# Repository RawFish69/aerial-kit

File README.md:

#  Aerial Kit

**UAS Controller, Planner, Simulator, Firmware & Configurator** - an open-source stack for aerial robots, from planning a path in simulation to configuring the flight controller.

## Demo

### Python simulation

Autonomous flight - plan a path, then fly it:

<table>
  <tr>
    <td width="50%" align="center"></td>
    <td width="50%" align="center"></td>
  </tr>
  <tr>
    <td valign="top"><em>RRT* through forest terrain on the RotorPy backend.</em></td>
    <td valign="top"><em>RRT* over mountains - the planner climbs a 47 m ridge to reach the goal. Planned path dashed in orange, flown trajectory in cyan.</em></td>
  </tr>
</table>

Standalone Python sim (Matplotlib 3D, follow camera):

<table>
  <tr>
    <td width="50%" align="center"></td>
    <td width="50%" align="center"></td>
  </tr>
  <tr>
    <td valign="top"><em>Native multirotor backend - a 56 m climbing turn, teal trail showing where it has flown. Each propeller is coloured by thrust (grey idle → yellow → orange → red).</em></td>
    <td valign="top"><em><a href="examples/fixed_wing">Twin-wing example</a> on the same renderer - banked 50° through the turn, flown path behind it, motors on the same colour map.</em></td>
  </tr>
</table>

### Custom 2.4 GHz LoRa / ELRS radio hardware

The Aerial Kit 2.4 GHz USB transceiver is a fabricated
**ESP32-S3-MINI-1U + SX1280 + RFX2401C** four-layer board. Its paired firmware
includes an RF-off hardware diagnostic plus separate ExpressLRS TX and RX
images, all built from a pinned upstream revision.

Fabricated Rev A3 boards: ESP32-S3 module and USB-C side, alongside the
SX1280/RFX2401C RF and control side.

<table>
  <tr>
    <td width="50%" align="center"></td>
    <td width="50%" align="center"></td>
  </tr>
  <tr>
    <td valign="top"><em>Rev A3 front: USB-C, ESP32-S3 module, role select, boot control and breakout pads.</em></td>
    <td valign="top"><em>Rev A3 back: SX1280 transceiver, RFX2401C front end, RF matching network and U.FL output.</em></td>
  </tr>
</table>

[Hardware sources and pinout](hardware/overlays/elrs-usb-tx/rev-a3/) ·
[Diagnostic, ExpressLRS TX and RX firmware](firmware/elrs-usb-tx-rev-a3/)

### Web configurator

[**Open the configurator**](https://rawfish69.github.io/aerial-kit/) · [Guide](docs/web-configurator.md)

Live attitude, receiver, sensors and parameter editing in the browser, over USB. Screenshots use the built-in demo board.

<table>
  <tr>
    <td width="50%"></td>
    <td width="50%"></td>
  </tr>
  <tr>
    <td><em>Classic theme.</em></td>
    <td><em>OG theme. A dark Modern theme is the default.</em></td>
  </tr>
</table>

### Hovering & Landing (IMU + Barometer + GPS)

https://github.com/user-attachments/assets/44837663-b281-45db-9803-5aaa9812833d

*Autonomous hover and landing, commanded over the CRSF/ESP-NOW link. The state estimate fuses IMU
attitude, barometric altitude, and GPS position.*

### ROS navigation

## What's in this repo

- **Controller** - standalone Python and ROS 2 control: PID, LQR, MPC, constrained MPC and MPPI, plus L1/TECS for fixed wing. The [`uav_control`](ros2_ws/src/uav_control/README.md) ROS 2 package flies missions with the constrained MPC or MPPI.
- **Planner** - straight, A*, RRT, RRT* and Dubins paths with shared terrain models.
- **Simulator** - Python simulation without ROS, plus ROS 2 fast, Gazebo and MuJoCo backends: FPV, micro long-range, research hex/octo multirotors and twin/single-motor flying wings, flyable autonomously or by keyboard.
- **AK Firmware** - our custom C flight controller, for Feather F405 and ESP32DEV, with a portable control core and image checks.
- **ELRS USB TX Rev A3** - custom ESP32-S3 + SX1280 + RFX2401C transceiver
  hardware and pinned ExpressLRS firmware target.
- **Web configurator** - live attitude, diagnostics and parameter editing over USB or a local bridge; includes a demo board.

The ROS-free control package is also on [PyPI](https://pypi.org/project/aerial-kit/): `pip install aerial-kit` or `pip install "aerial-kit[sim]"`.

## Autopilot & firmware support

| Platform | Integration | Guide |
| --- | --- | --- |
| **AK Firmware** | Custom flight-controller firmware + web configurator | [Guide](docs/flight-controller-firmware.md) |
| Betaflight | CRSF over ESP-NOW / UDP relay | [Guide](docs/HARDWARE.md) |
| PX4 | MAVLink over USB / UART / telemetry radio | [Guide](ros2_ws/src/mavlink_bridge/README.md) |
| ArduPilot | MAVLink through the same backend | [Guide](ros2_ws/src/mavlink_bridge/README.md) |
| ESP32 radio links | ESP-NOW, ELRS, LoRa and GPS | [Guide](firmware/legacy/README.md) |
| **Aerial Kit ELRS USB TX Rev A3** | Custom hardware, RF-off diagnostic, ELRS TX/RX images and native-USB bench tools | [Firmware](firmware/elrs-usb-tx-rev-a3/README.md) · [Bench](docs/RADIO-BENCH.md) |
| **Python protocol clients** | CRSF, Aerial Kit, MAVLink and gated-write MSP | [Protocol guide](docs/PROTOCOLS.md) |

## Start here

| Explore | Guide |
| --- | --- |
| Run a simulator or controller | [Software guide](docs/SOFTWARE_GUIDE.md) · [Examples](docs/EXAMPLE_USAGE.md) |
| Build AK firmware | [Firmware quick start & board status](docs/flight-controller-firmware.md) |
| Configure a board | [Web configurator quick start](docs/web-configurator.md) · [Build & deployment](apps/configurator/docs/BUILD-AND-DEPLOY.md) |
| Connect Python to firmware | [USB telemetry and attitude example](examples/firmware/) |
| Hardware designs and overlays | [Hardware workspace](hardware/) |
| Understand the stack | [Architecture, airframes, ROS 2 and roadmap](docs/STACK-GUIDE.md) |
| Connect hardware | [Hardware guide](docs/HARDWARE.md) · [Radio firmware](firmware/legacy/README.md) |
| Query radios and vehicles from Python | [Protocol examples](examples/comms/) · [Protocol guide](docs/PROTOCOLS.md) |
| Use the logo | [Branding & SVG assets](docs/branding.md) |

## Python protocol client

`aerial_kit.comms` provides one Python boundary for ELRS/CRSF radios, Aerial
Kit and Betaflight flight controllers, PX4/ArduPilot over MAVLink, and MSP
devices. Reads are safe by default; every mutation has an explicit gate.
The console can query a radio or flight controller directly:

```bash
pip install "aerial-kit[radio,mavlink]"
ak radio status --port /dev/ttyACM0
ak radio uid --port /dev/ttyACM0 --role tx
ak radio uid --port /dev/ttyACM1 --role rx
ak radio diag --port /dev/ttyACM0 --role tx
ak radio monitor --port /dev/ttyACM0 --duration 5 --json monitor.json
ak radio drive --port /dev/ttyACM0 --hz 150 --duration 10 --write
ak radio drive --port /dev/ttyACM0 --profile betaflight --write
ak radio teleop --port /dev/ttyACM0 --profile betaflight --duration 30 --write --confirm-arm
ak doctor                                   # list serial endpoints, no port opening
ak doctor --probe /dev/ttyACM0              # read-only radio/AKP/Betaflight probe
ak fc status --port /dev/ttyACM0             # auto-detects AKP or MSP
ak fc status --port /dev/ttyACM0 --protocol betaflight
ak fc params --port /dev/ttyACM0             # Aerial Kit indexed table
ak fc params --port /dev/ttyACM0 --name failsafe_throttle
ak fc get failsafe_throttle --port /dev/ttyACM0
ak fc set failsafe_throttle 1200 --port /dev/ttyACM0 --write
ak fc save --port /dev/ttyACM0 --write
ak fc preflight --port /dev/ttyACM0 --protocol betaflight --json fc-preflight.json
ak fc rc --port /dev/ttyACM0 --protocol betaflight --json fc-rc.json
ak sim --no-show
```

Use `--radio /dev/ttyUSB0` with `fc` to carry Aerial Kit requests over an ELRS
link. `fc` auto-detects Aerial Kit AKP and Betaflight MSP; `--protocol akp` or
`--protocol betaflight` removes the probe wait. MSP has no command that lists
all setting names, so Betaflight settings are read by name. Mutations require
`--write`; omitting it refuses before a frame is sent, and the CLI also refuses
configuration writes while the board reports itself armed. A successful
Betaflight setting reply is the read-back, while save remains a separate
`MSP_EEPROM_WRITE` operation. Bind and UID writes reconnect after the module
reboot and fail unless the six-byte UID reads back exactly. `aerial-kit-link`,
`aerial-kit-sim` and `aerial-kit-teleop` remain compatibility commands; new
scripts should use `ak`.

Betaflight MSP status does not contain a receiver-link-live field. `ak fc
status` therefore prints `link=unknown` for Betaflight instead of inferring a
healthy link from a successful USB response. Use `ak fc rc` for a fresh channel
observation and `ak fc preflight` to decode Betaflight arming-disable flags;
failsafe and receiver-failsafe bits make preflight exit nonzero.

`ak radio teleop` is the live keyboard path through a CRSF transmitter. It
starts disarmed; press Enter to arm after the low-throttle hold. A/D, W/S and
Q/E step roll, pitch and yaw, R/F change throttle, C neutralises the sticks,
and X immediately disarms and exits. Timeout, Ctrl-C, panic and transport
errors all attempt a final disarmed frame. The command is bounded by
`--duration` and requires both `--write` and `--confirm-arm`. The existing
`ak teleop` command remains simulator-only.

`ak doctor` lists `/dev/serial/by-id` aliases, raw ACM/USB paths, read/write
permissions and optional protocol dependencies without opening a port. Add
`--probe PATH` only when a read-only identification attempt is intended; it
tries CRSF device information, Aerial Kit AKP and Betaflight MSP in that order.

See [docs/PROTOCOLS.md](docs/PROTOCOLS.md) for framing,
transport and safety details. Native-USB radio monitor, drive, capture,
telemetry injection and two-board evidence are covered in
[docs/RADIO-BENCH.md](docs/RADIO-BENCH.md).

## Licence

The Python/ROS stack and existing link projects retain the root [MIT licence](LICENSE). AK flight-controller firmware and the web configurator are **GPL-3.0-or-later**, each with its own [firmware](firmware/LICENSE) and [configurator](apps/configurator/LICENSE) licence. Third-party notices stay with their components.

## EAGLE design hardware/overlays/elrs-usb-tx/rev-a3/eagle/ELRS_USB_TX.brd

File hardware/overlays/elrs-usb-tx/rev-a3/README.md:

# ELRS USB TX · AERIAL KIT REV A3

This is the hardware and Ubuntu handoff for the fabricated ELRS USB TX project in Autodesk Fusion. The recovered design is marked **AERIAL KIT / REV A3 / 2.4GHz TRANSCEIVER**. Compare that silkscreen and the actual population to this design before powering or programming a unit. The user reports fabrication is complete. Assembly, board measurements, flash contents and RF operation have yet to be verified.

The corresponding Aerial Kit firmware, diagnostic and build instructions are
under [`firmware/elrs-usb-tx-rev-a3/`](../../../../firmware/elrs-usb-tx-rev-a3/).
The hardware sources are author-supplied; no hardware licence has been
asserted yet.

## Start here

- [Ubuntu bring-up and flashing](UBUNTU-BRINGUP.md) has the USB ROM boot procedure, read-only identification, flash backup and UART recovery.
- [Hardware reference](HARDWARE.md) has the GPIO assignments, headers, test pads, power and RF design.
- [Fusion 3D preview](previews/3d-board-big.png) is a CAD view of the assembly.
- [Component list and coordinates](data/components.csv), [ESP32 pin map](data/esp32-pin-map.csv), [schematic nets](data/schematic-nets.csv), [PCB nets](data/pcb-nets.csv), [EDA rules](data/design-rules.csv), [silkscreen](data/layout-silkscreen.csv) and [schematic sheet notes](data/schematic-notes.md) are the machine-readable or text references.

## CAD and provenance

- `eagle/ELRS_USB_TX.sch` and `eagle/ELRS_USB_TX.brd` are the paired EAGLE XML documents embedded in Fusion's cached schematic and board containers. Both are byte-for-byte identical to the corresponding files in Fusion's temporary Electronics output. The project library is embedded. Use the XML directly for analysis on Ubuntu or import the pair into a compatible PCB editor. Verify any imported geometry against Fusion, particularly Fusion-specific pours and slots.
- `fusion-cache/` holds the original cached electronics project (`.fprj`), schematic (`.fsch`), PCB (`.fbrd`) and 3D PCB (`.f3d`). These individually passed archive integrity checks. Cloud reference resolution and re-import of the cache copies have yet to be tested.
- The schematic contains five sheets. All 87 PCB elements have matching schematic references and values. All 60 nets agree at the pad level after resolving schematic pins through the embedded device mappings. [Comparison result](data/connectivity-comparison.json).
- Availability of the exact order-submitted Gerbers, drill files, fabrication stackup, supplier BOM, placement files, serial/lab logs, board photos and verified firmware image remains open. The component CSV gives CAD values, footprints and positions. Confirm supplier part numbers and assembly exceptions from the order.
- `SHA256SUMS` records checksums for the handoff files. From its directory on Ubuntu, run `sha256sum -c SHA256SUMS`.

On Ubuntu, copy or extract the folder to a working directory. In WSL, the Windows copy is normally at `/mnt/c/PCB_Fusion/ELRS_USB_TX`. On native Ubuntu, use the mounted Windows volume's `PCB_Fusion/ELRS_USB_TX` or transfer the zip. Give the next agent this README and the bring-up guide.

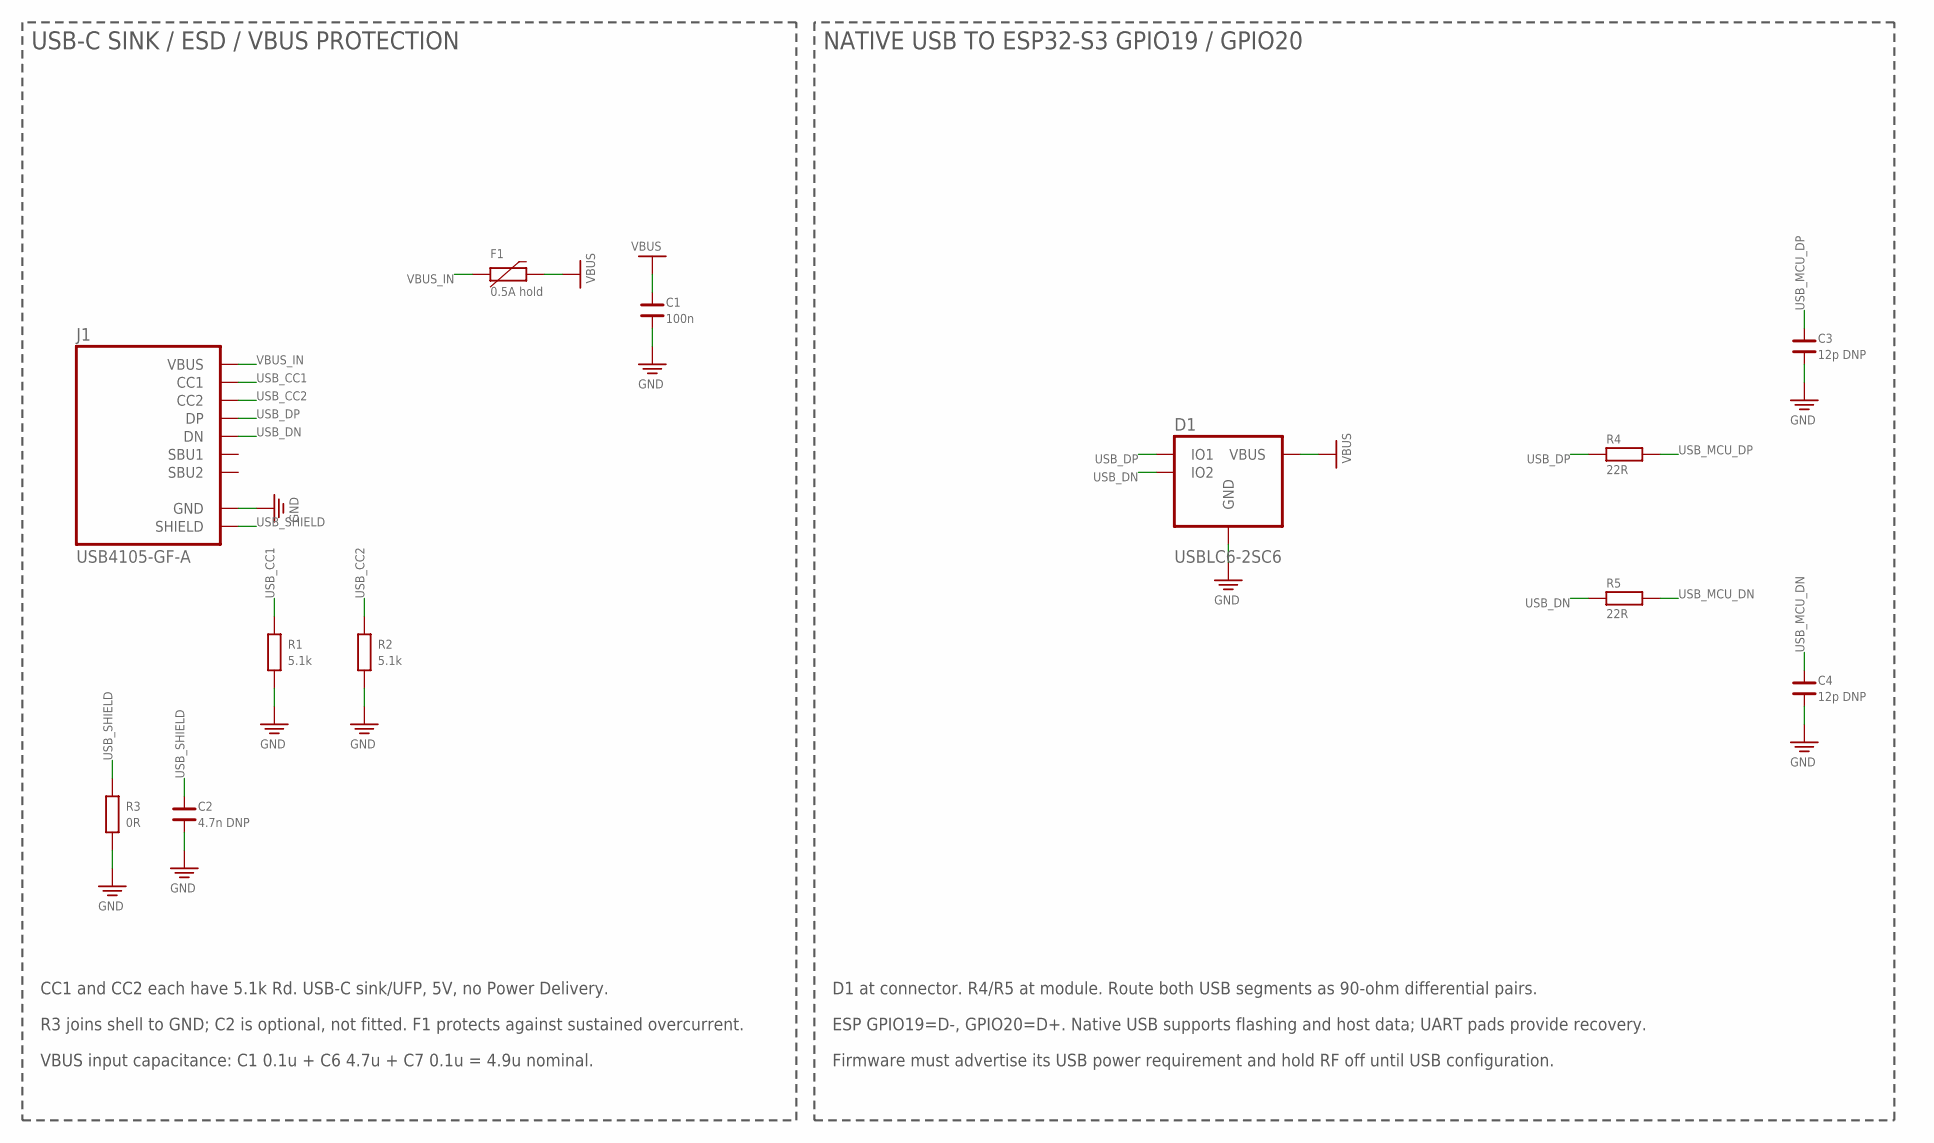
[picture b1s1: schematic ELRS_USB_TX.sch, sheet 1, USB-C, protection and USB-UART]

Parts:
C1: 100n; C0402; MPN CL05B104KO5NNNC; LCSC C1525
C2: 4.7n DNP; C0402; MPN CL05B472KB5NNNC; LCSC C84705
C3, C4: 12p DNP; C0402; MPN GRM1555C1H120JA01D; LCSC C76948
D1: USBLC6-2SC6; SOT23-6; MPN USBLC6-2SC6; LCSC C7519
F1: 0.5A hold; F0805; MPN 0805L050WR; LCSC C207022
J1: USB4105-GF-A; USB4105_GF_A; MPN USB4105-GF-A; LCSC C3020560
R1, R2: 5.1k; R0402; MPN 0402WGF5101TCE; LCSC C25905
R3: 0R; R0402; MPN 0402WGF0000TCE; LCSC C17168
R4, R5: 22R; R0402; MPN 0402WGF220JTCE; LCSC C25092

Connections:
GND: C1.1, C2.1, C3.1, C4.1, D1.2 (GND), J1.A1B12 (GND), J1.B12A1 (GND), R1.1, R2.1, R3.1; also elsewhere on the board
USB_CC1: J1.A5 (CC1), R1.2
USB_CC2: J1.B5 (CC2), R2.2
USB_DN: D1.3 (IO2), D1.4 (IO2), J1.A7 (DN), J1.B7 (DN), R5.1
USB_DP: D1.1 (IO1), D1.6 (IO1), J1.A6 (DP), J1.B6 (DP), R4.1
USB_MCU_DN: C4.2, R5.2; also elsewhere on the board
USB_MCU_DP: C3.2, R4.2; also elsewhere on the board
USB_SHIELD: C2.2, J1.S1 (SHIELD), J1.S1B (SHIELD), J1.S1T (SHIELD), J1.S2 (SHIELD), J1.S2B (SHIELD), J1.S2T (SHIELD), J1.S3 (SHIELD), J1.S3B (SHIELD), J1.S3T (SHIELD), J1.S4 (SHIELD), J1.S4B (SHIELD), J1.S4T (SHIELD), R3.2
VBUS: C1.2, D1.5 (VBUS), F1.2; also elsewhere on the board
VBUS_IN: F1.1, J1.A4B9 (VBUS), J1.B9A4 (VBUS)

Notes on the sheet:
USB-C SINK / ESD / VBUS PROTECTION
NATIVE USB TO ESP32-S3 GPIO19 / GPIO20
CC1 and CC2 each have 5.1k Rd. USB-C sink/UFP, 5V, no Power Delivery.
R3 joins shell to GND; C2 is optional, not fitted. F1 protects against sustained overcurrent.
VBUS input capacitance: C1 0.1u + C6 4.7u + C7 0.1u = 4.9u nominal.
D1 at connector. R4/R5 at module. Route both USB segments as 90-ohm differential pairs.
ESP GPIO19=D-, GPIO20=D+. Native USB supports flashing and host data; UART pads provide recovery.
Firmware must advertise its USB power requirement and hold RF off until USB configuration.

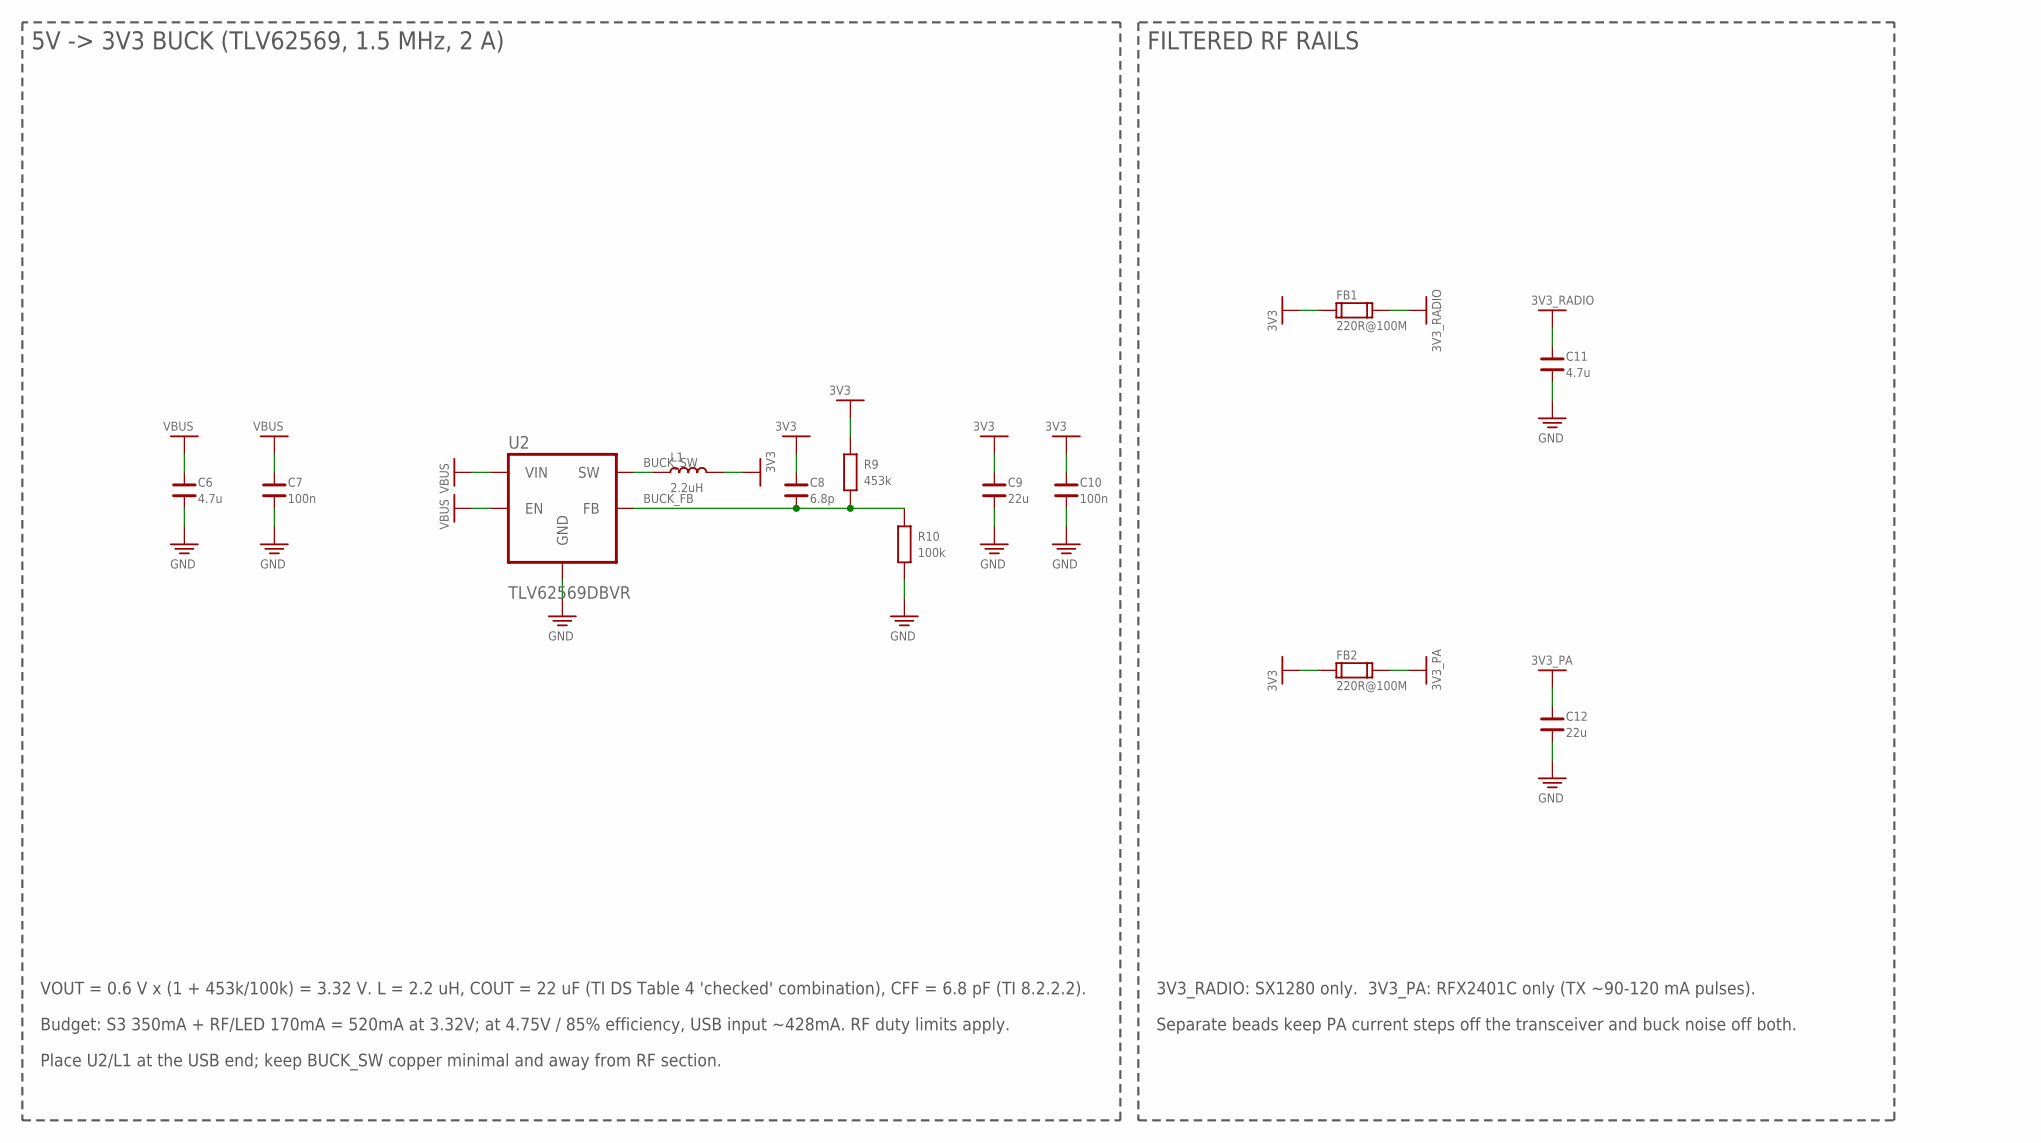
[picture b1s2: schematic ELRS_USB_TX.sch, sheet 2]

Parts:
C6, C11: 4.7u; C0603; MPN CL10A475KO8NNNC; LCSC C19666
C7, C10: 100n; C0402; MPN CL05B104KO5NNNC; LCSC C1525
C8: 6.8p; C0402; MPN GRM1555C1H6R8DA01D; LCSC C237286
C9, C12: 22u; C0805; MPN CL21A226MAQNNNE; LCSC C45783
FB1, FB2: 220R@100M; FB0603; MPN BLM18PG221SN1D; LCSC C80165
L1: 2.2uH; DFE201610; MPN DFE201610E-2R2M=P2; LCSC C337891
R9: 453k; R0402; MPN 0402WGF4533TCE; LCSC C27009
R10: 100k; R0402; MPN 0402WGF1003TCE; LCSC C25741
U2: TLV62569DBVR; SOT23-5; MPN TLV62569DBVR; LCSC C141836

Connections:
3V3: C8.2, C9.2, C10.2, FB1.1, FB2.1, L1.2, R9.2; also elsewhere on the board
3V3_PA: C12.2, FB2.2; also elsewhere on the board
3V3_RADIO: C11.2, FB1.2; also elsewhere on the board
BUCK_FB: C8.1, R9.1, R10.2, U2.5 (FB)
BUCK_SW: L1.1, U2.3 (SW)
GND: C6.1, C7.1, C9.1, C10.1, C11.1, C12.1, R10.1, U2.2 (GND); also elsewhere on the board
VBUS: C6.2, C7.2, U2.1 (EN), U2.4 (VIN); also elsewhere on the board

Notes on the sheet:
5V -> 3V3 BUCK (TLV62569, 1.5 MHz, 2 A)
FILTERED RF RAILS
VOUT = 0.6 V x (1 + 453k/100k) = 3.32 V. L = 2.2 uH, COUT = 22 uF (TI DS Table 4 'checked' combination), CFF = 6.8 pF (TI 8.2.2.2).
Budget: S3 350mA + RF/LED 170mA = 520mA at 3.32V; at 4.75V / 85% efficiency, USB input ~428mA. RF duty limits apply.
Place U2/L1 at the USB end; keep BUCK_SW copper minimal and away from RF section.
3V3_RADIO: SX1280 only. 3V3_PA: RFX2401C only (TX ~90-120 mA pulses).
Separate beads keep PA current steps off the transceiver and buck noise off both.

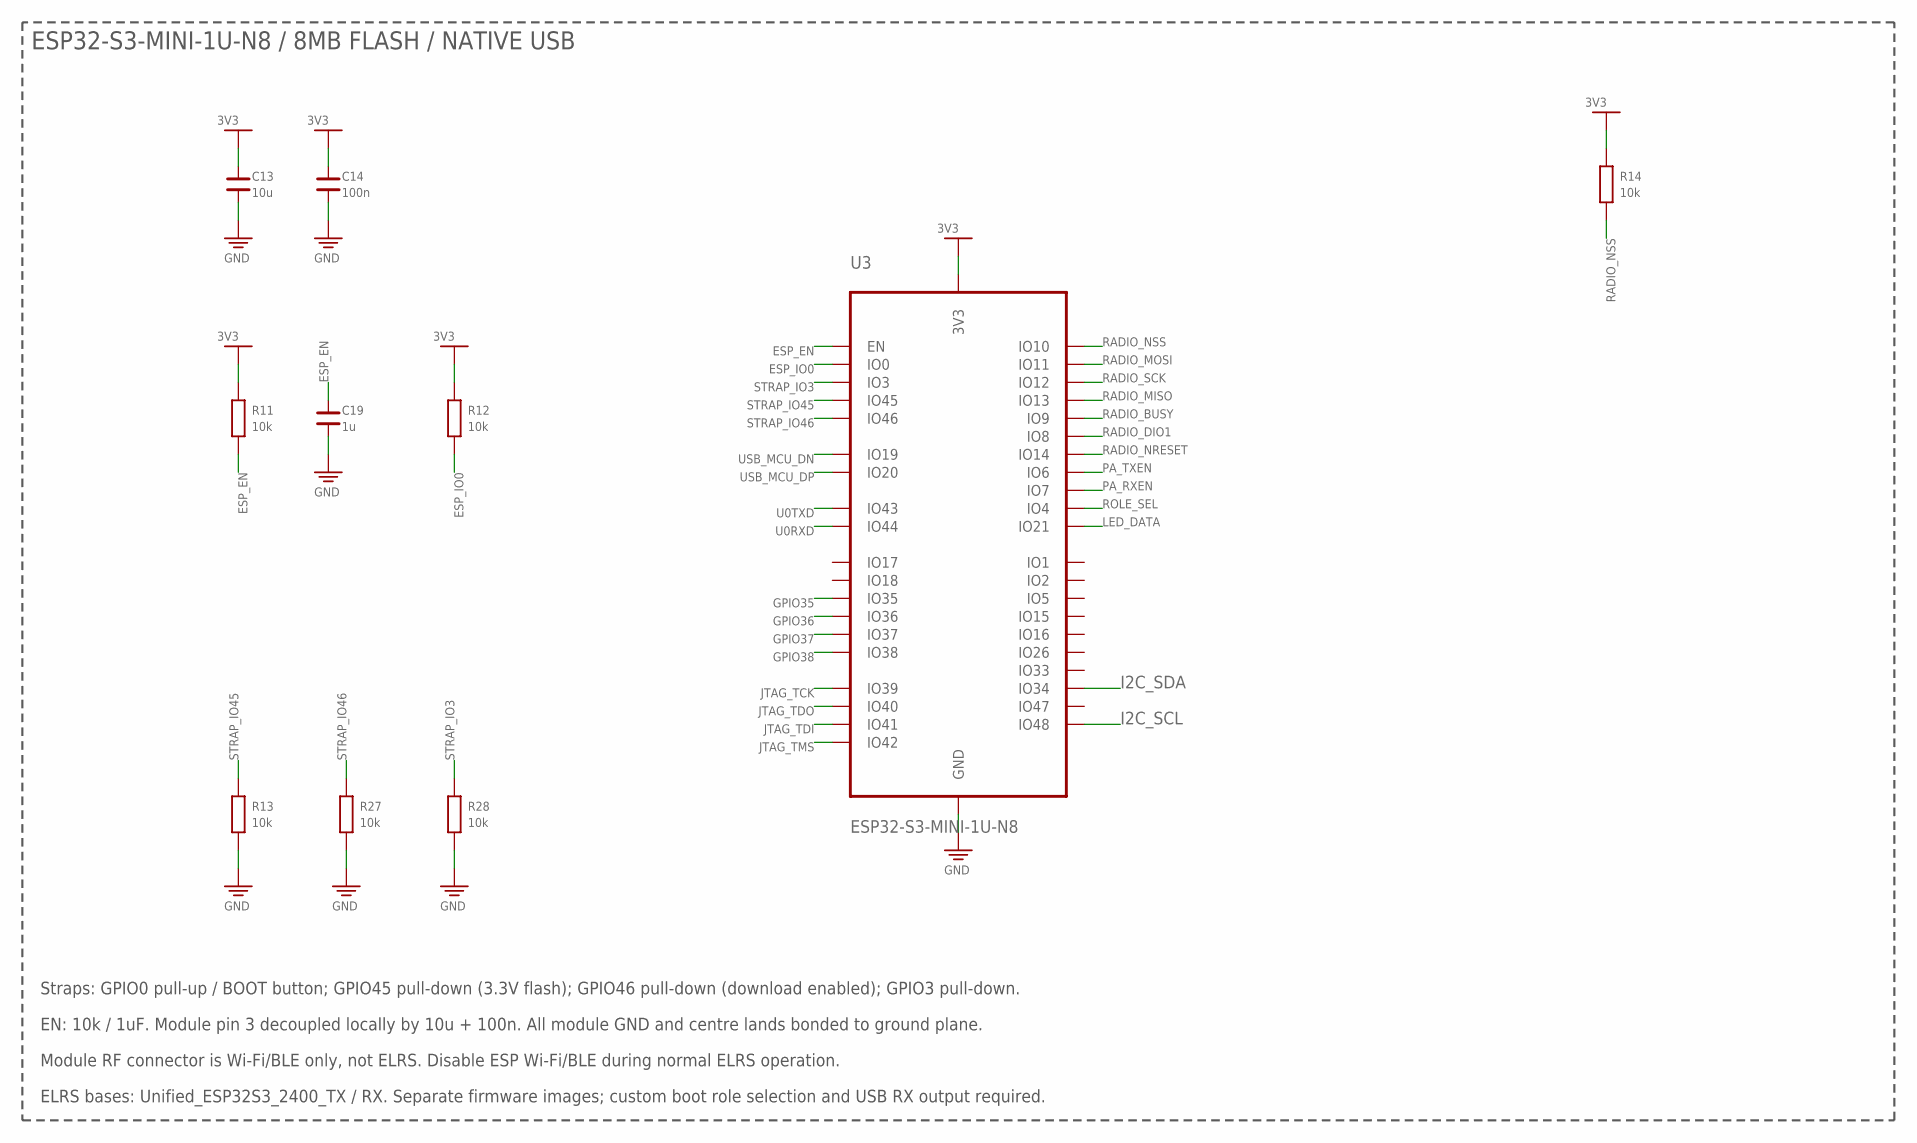
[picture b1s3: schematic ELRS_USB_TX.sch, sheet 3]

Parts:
C13: 10u; C0603; MPN CL10A106KP8NNNC; LCSC C19702
C14: 100n; C0402; MPN CL05B104KO5NNNC; LCSC C1525
C19: 1u; C0402; MPN CL05A105KA5NQNC; LCSC C52923
R11, R12, R13, R14, R27, R28: 10k; R0402; MPN 0402WGF1002TCE; LCSC C25744
U3: ESP32-S3-MINI-1U-N8; ESP32_S3_MINI_1U; MPN ESP32-S3-MINI-1U-N8; LCSC C2980299

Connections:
3V3: C13.2, C14.2, R11.2, R12.2, R14.2, U3.3 (3V3); also elsewhere on the board
ESP_EN: C19.2, R11.1, U3.45 (EN); also elsewhere on the board
ESP_IO0: R12.1, U3.4 (IO0); also elsewhere on the board
GND: C13.1, C14.1, C19.1, R13.1, R27.1, R28.1, U3.1 (GND), U3.2 (GND), U3.42 (GND), U3.43 (GND), U3.46 (GND), U3.47 (GND), U3.48 (GND), U3.49 (GND), U3.50 (GND), U3.51 (GND), U3.52 (GND), U3.53 (GND), U3.54 (GND), U3.55 (GND), U3.56 (GND), U3.57 (GND), U3.58 (GND), U3.59 (GND), U3.60 (GND), U3.61_1 (GND), U3.61_2 (GND), U3.61_3 (GND), U3.61_4 (GND), U3.61_5 (GND), U3.61_6 (GND), U3.61_7 (GND), U3.61_8 (GND), U3.61_9 (GND), U3.62 (GND), U3.63 (GND), U3.64 (GND), U3.65 (GND); also elsewhere on the board
GPIO35: U3.31 (IO35); also elsewhere on the board
GPIO36: U3.32 (IO36); also elsewhere on the board
GPIO37: U3.33 (IO37); also elsewhere on the board
GPIO38: U3.34 (IO38); also elsewhere on the board
I2C_SCL: U3.30 (IO48); also elsewhere on the board
I2C_SDA: U3.29 (IO34); also elsewhere on the board
JTAG_TCK: U3.35 (IO39); also elsewhere on the board
JTAG_TDI: U3.37 (IO41); also elsewhere on the board
JTAG_TDO: U3.36 (IO40); also elsewhere on the board
JTAG_TMS: U3.38 (IO42); also elsewhere on the board
LED_DATA: U3.25 (IO21); also elsewhere on the board
PA_RXEN: U3.11 (IO7); also elsewhere on the board
PA_TXEN: U3.10 (IO6); also elsewhere on the board
RADIO_BUSY: U3.13 (IO9); also elsewhere on the board
RADIO_DIO1: U3.12 (IO8); also elsewhere on the board
RADIO_MISO: U3.17 (IO13); also elsewhere on the board
RADIO_MOSI: U3.15 (IO11); also elsewhere on the board
RADIO_NRESET: U3.18 (IO14); also elsewhere on the board
RADIO_NSS: R14.1, U3.14 (IO10); also elsewhere on the board
RADIO_SCK: U3.16 (IO12); also elsewhere on the board
ROLE_SEL: U3.8 (IO4); also elsewhere on the board
STRAP_IO3: R28.2, U3.7 (IO3)
STRAP_IO45: R13.2, U3.41 (IO45)
STRAP_IO46: R27.2, U3.44 (IO46)
U0RXD: U3.40 (IO44); also elsewhere on the board
U0TXD: U3.39 (IO43); also elsewhere on the board
USB_MCU_DN: U3.23 (IO19); also elsewhere on the board
USB_MCU_DP: U3.24 (IO20); also elsewhere on the board

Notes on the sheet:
ESP32-S3-MINI-1U-N8 / 8MB FLASH / NATIVE USB
Straps: GPIO0 pull-up / BOOT button; GPIO45 pull-down (3.3V flash); GPIO46 pull-down (download enabled); GPIO3 pull-down.
EN: 10k / 1uF. Module pin 3 decoupled locally by 10u + 100n. All module GND and centre lands bonded to ground plane.
Module RF connector is Wi-Fi/BLE only, not ELRS. Disable ESP Wi-Fi/BLE during normal ELRS operation.
ELRS bases: Unified_ESP32S3_2400_TX / RX. Separate firmware images; custom boot role selection and USB RX output required.

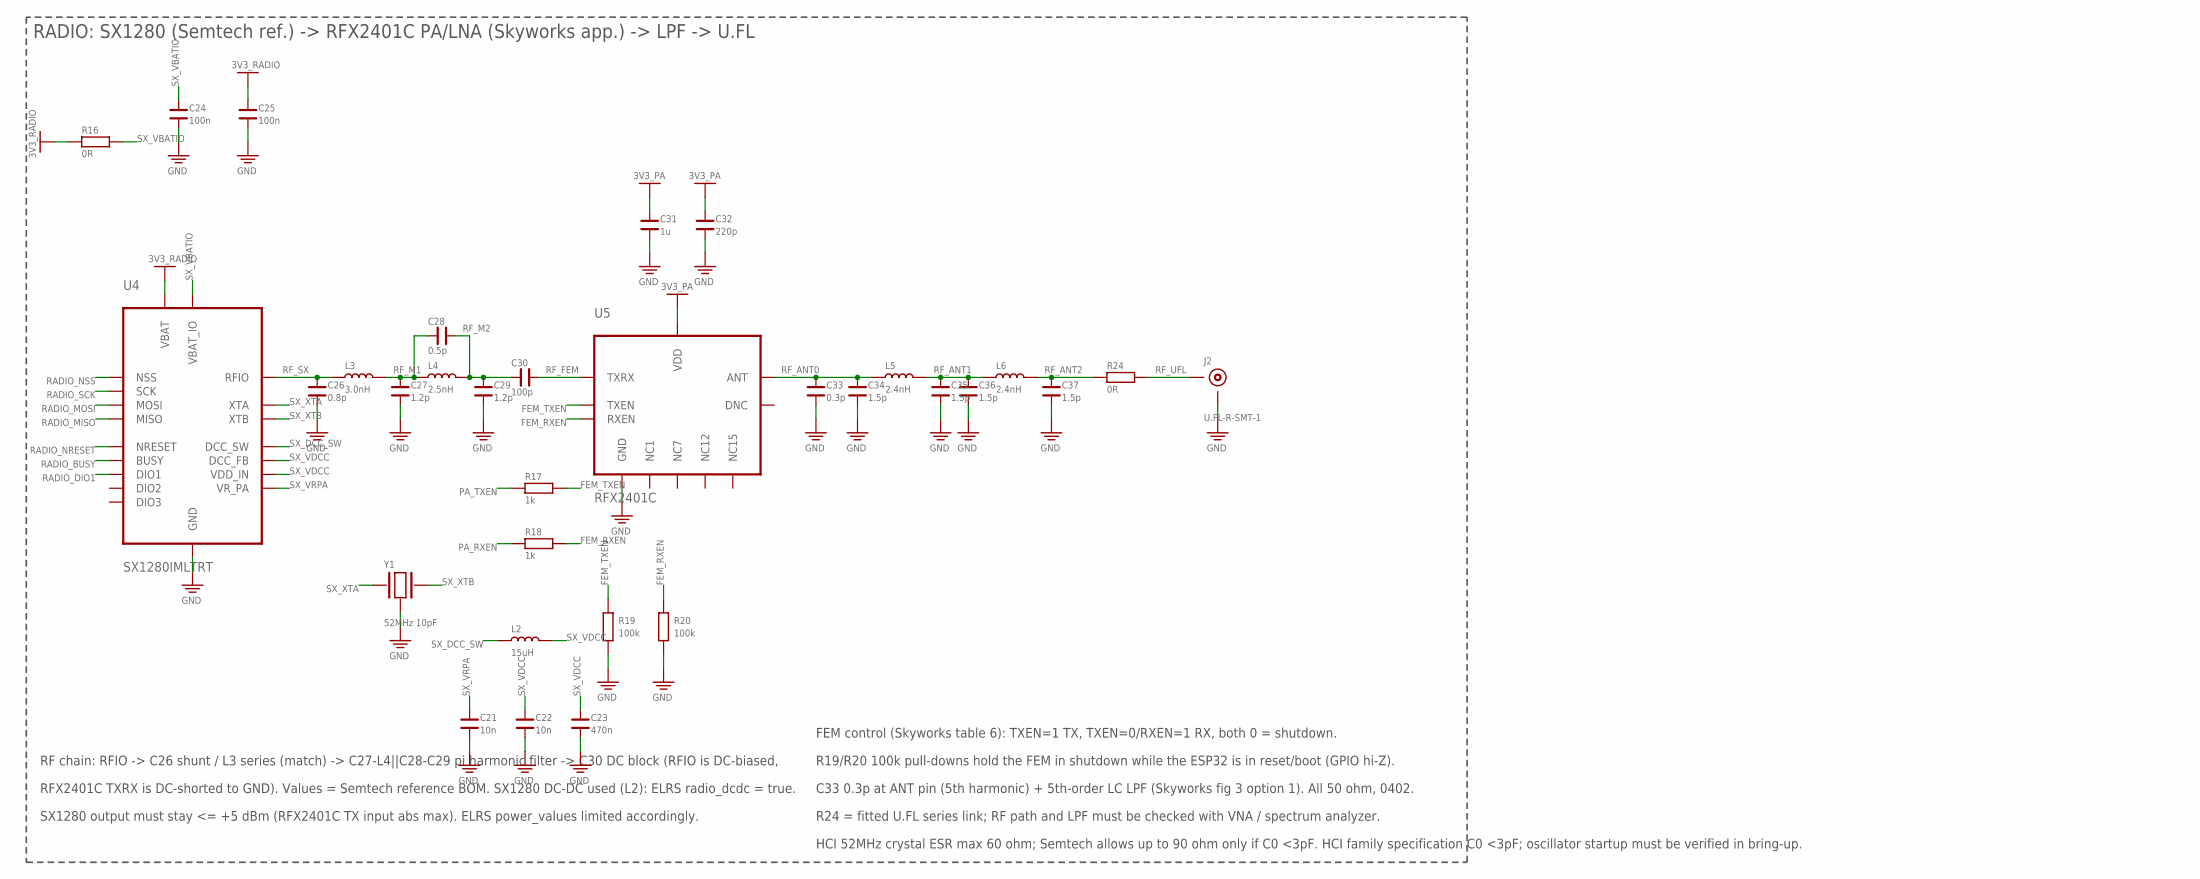
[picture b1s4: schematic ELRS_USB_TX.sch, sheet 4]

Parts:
C21, C22: 10n; C0402; MPN CL05B103KB5NNNC; LCSC C15195
C23: 470n; C0402; MPN GRM155R61A474KE15D; LCSC C77003
C24, C25: 100n; C0402; MPN CL05B104KO5NNNC; LCSC C1525
C26: 0.8p; C0402; MPN GRM1555C1HR80BA01D; LCSC C76988
C27, C29: 1.2p; C0402; MPN GRM1555C1H1R2CA01D; LCSC C76955
C28: 0.5p; C0402; MPN GRM1555C1HR50BA01D; LCSC C77179
C30: 100p; C0402; MPN GRM1555C1H101JA01D; LCSC C77177
C31: 1u; C0402; MPN CL05A105KA5NQNC; LCSC C52923
C32: 220p; C0402; MPN CL05C221JB5NNNC; LCSC C307445
C33: 0.3p; C0402; MPN GRM1555C1HR30WA01D; LCSC C92338
C34, C35, C36, C37: 1.5p; C0402; MPN GRM1555C1H1R5BA01D; LCSC C76957
J2: U.FL-R-SMT-1; UFL_R_SMT; MPN U.FL-R-SMT-1(80); LCSC C88374
L2: 15uH; L0805; MPN MLZ2012M150WT000; LCSC C383402
L3: 3.0nH; L0402; MPN LQW15AN3N0B80D; LCSC C2041661
L4: 2.5nH; L0402; MPN LQW15AN2N5C00D; LCSC C703121
L5, L6: 2.4nH; L0402; MPN LQG15HN2N4B02D; LCSC C3911311
R16, R24: 0R; R0402; MPN 0402WGF0000TCE; LCSC C17168
R17, R18: 1k; R0402; MPN 0402WGF1001TCE; LCSC C11702
R19, R20: 100k; R0402; MPN 0402WGF1003TCE; LCSC C25741
U4: SX1280IMLTRT; QFN24_4X4_SX1280; MPN SX1280IMLTRT; LCSC C125969
U5: RFX2401C; QFN16_3X3_RFX2401C; MPN RFX2401C; LCSC C19213
Y1: 52MHz 10pF; XTAL2016_4P; MPN XC21M4-52.000-F10NNHPL; LCSC C3034316

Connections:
3V3_PA: C31.2, C32.2, U5.14 (VDD), U5.16 (VDD); also elsewhere on the board
3V3_RADIO: C25.2, R16.1, U4.15 (VBAT); also elsewhere on the board
FEM_RXEN: R18.2, R20.2, U5.6 (RXEN)
FEM_TXEN: R17.2, R19.2, U5.5 (TXEN)
GND: C21.1, C22.1, C23.1, C24.1, C25.1, C26.1, C27.1, C29.1, C31.1, C32.1, C33.1, C34.1, C35.1, C36.1, C37.1, J2.GND1 (GND), J2.GND2 (GND), R19.1, R20.1, U4.5 (GND), U4.13 (GND), U4.20 (GND), U4.21 (GND), U4.23 (GND), U4.24 (GND), U4.25 (GND), U5.2 (GND), U5.3 (GND), U5.8 (GND), U5.9 (GND), U5.11 (GND), U5.17 (GND), Y1.2 (GND), Y1.4 (GND); also elsewhere on the board
PA_RXEN: R18.1; also elsewhere on the board
PA_TXEN: R17.1; also elsewhere on the board
RADIO_BUSY: U4.7 (BUSY); also elsewhere on the board
RADIO_DIO1: U4.8 (DIO1); also elsewhere on the board
RADIO_MISO: U4.16 (MISO); also elsewhere on the board
RADIO_MOSI: U4.17 (MOSI); also elsewhere on the board
RADIO_NRESET: U4.3 (NRESET); also elsewhere on the board
RADIO_NSS: U4.19 (NSS); also elsewhere on the board
RADIO_SCK: U4.18 (SCK); also elsewhere on the board
RF_ANT0: C33.2, C34.2, L5.1, U5.10 (ANT)
RF_ANT1: C35.2, C36.2, L5.2, L6.1
RF_ANT2: C37.2, L6.2, R24.1
RF_FEM: C30.2, U5.4 (TXRX)
RF_M1: C27.2, C28.1, L3.2, L4.1
RF_M2: C28.2, C29.2, C30.1, L4.2
RF_SX: C26.2, L3.1, U4.22 (RFIO)
RF_UFL: J2.SIG, R24.2
SX_DCC_SW: L2.1, U4.14 (DCC_SW)
SX_VBATIO: C24.2, R16.2, U4.11 (VBAT_IO)
SX_VDCC: C22.2, C23.2, L2.2, U4.2 (VDD_IN), U4.12 (DCC_FB)
SX_VRPA: C21.2, U4.1 (VR_PA)
SX_XTA: U4.4 (XTA), Y1.1 (X1)
SX_XTB: U4.6 (XTB), Y1.3 (X2)

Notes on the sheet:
RADIO: SX1280 (Semtech ref.) -> RFX2401C PA/LNA (Skyworks app.) -> LPF -> U.FL
RF chain: RFIO -> C26 shunt / L3 series (match) -> C27-L4||C28-C29 pi harmonic filter -> C30 DC block (RFIO is DC-biased,
RFX2401C TXRX is DC-shorted to GND). Values = Semtech reference BOM. SX1280 DC-DC used (L2): ELRS radio_dcdc = true.
SX1280 output must stay <= +5 dBm (RFX2401C TX input abs max). ELRS power_values limited accordingly.
FEM control (Skyworks table 6): TXEN=1 TX, TXEN=0/RXEN=1 RX, both 0 = shutdown.
R19/R20 100k pull-downs hold the FEM in shutdown while the ESP32 is in reset/boot (GPIO hi-Z).
C33 0.3p at ANT pin (5th harmonic) + 5th-order LC LPF (Skyworks fig 3 option 1). All 50 ohm, 0402.
R24 = fitted U.FL series link; RF path and LPF must be checked with VNA / spectrum analyzer.
HCI 52MHz crystal ESR max 60 ohm; Semtech allows up to 90 ohm only if C0 <3pF. HCI family specification C0 <3pF; oscillator startup must be verified in bring-up.

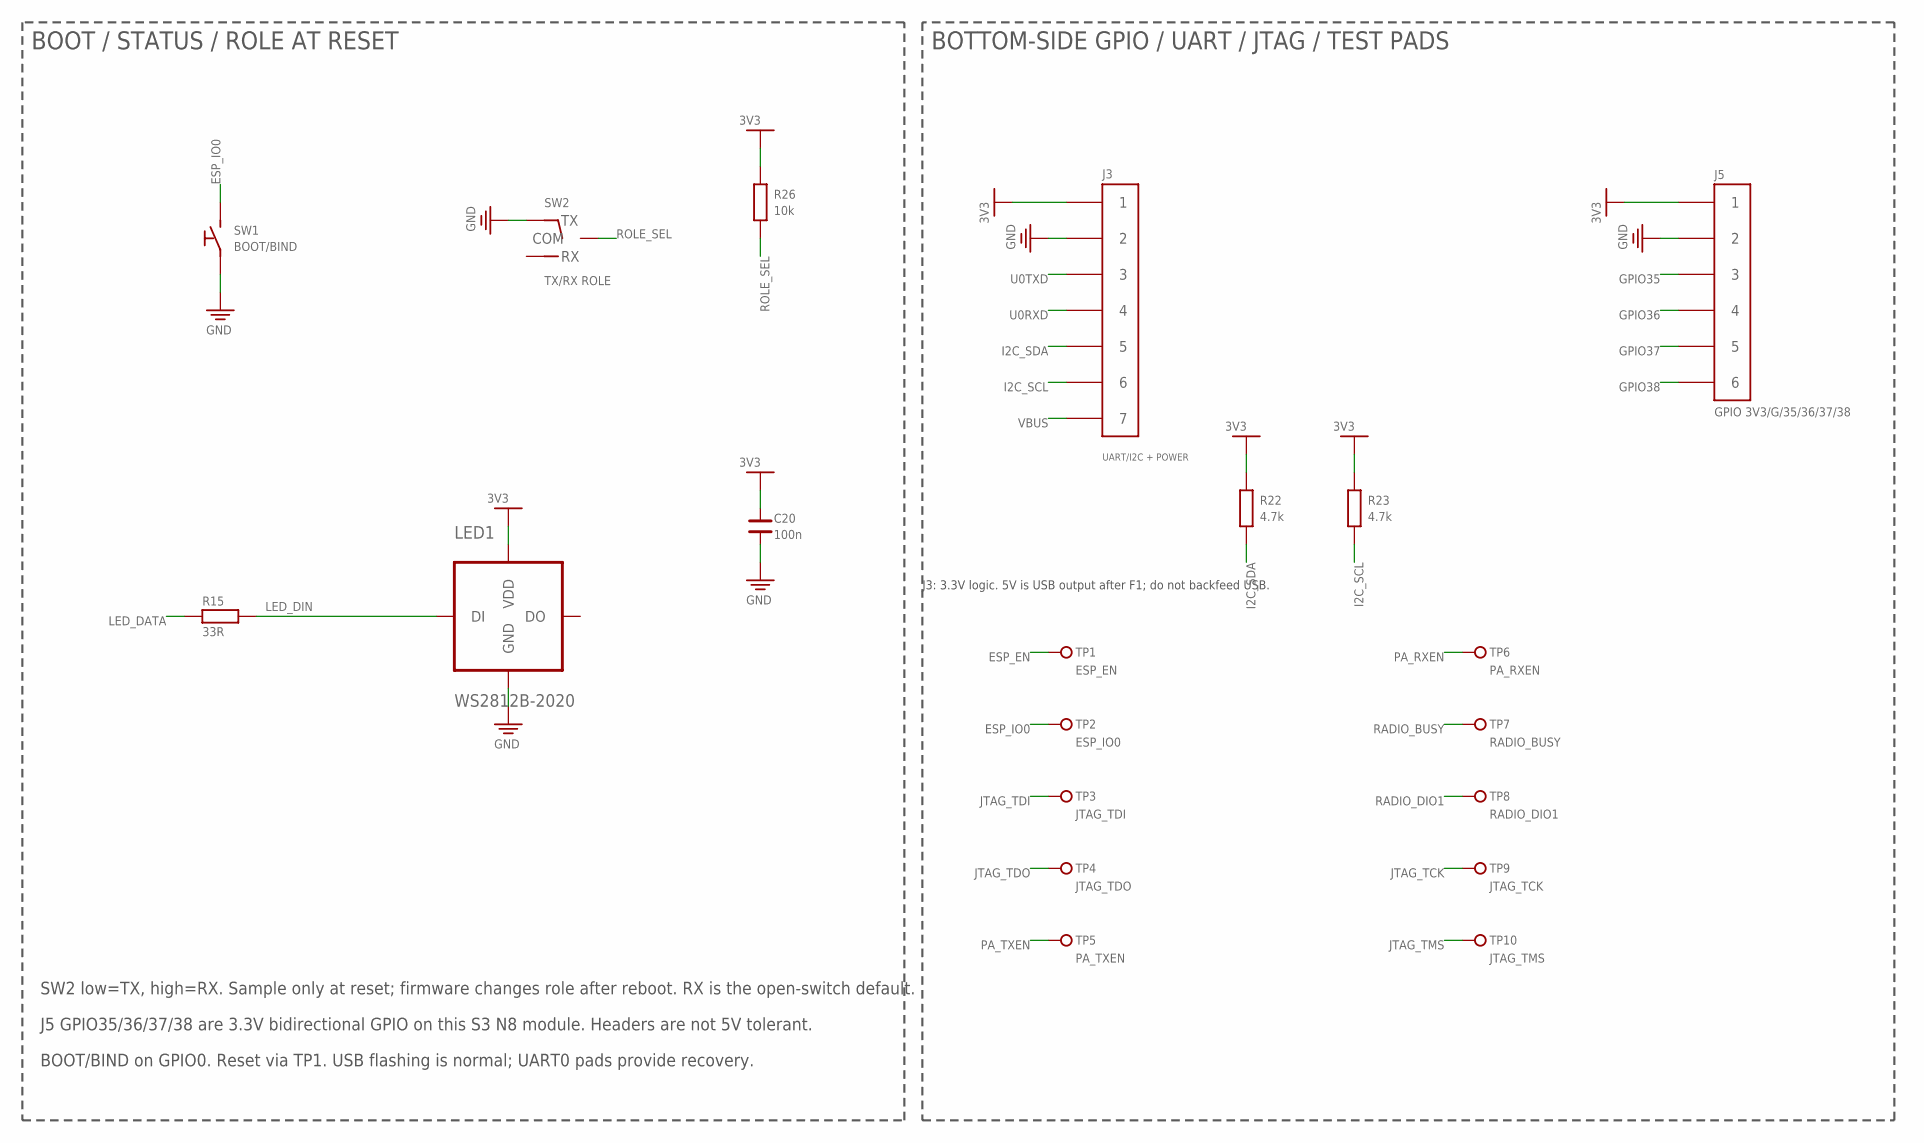
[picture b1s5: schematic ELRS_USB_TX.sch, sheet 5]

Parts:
C20: 100n; C0402; MPN CL05B104KO5NNNC; LCSC C1525
J3: UART/I2C + POWER; PADS7_1P5; MPN bare pads
J5: GPIO 3V3/G/35/36/37/38; PADS6_1P5; MPN bare pads
LED1: WS2812B-2020; LED2020_WS2812B; MPN WS2812B-2020-V6; LCSC C52917434
R15: 33R; R0402; MPN 0402WGF330JTCE; LCSC C25105
R22, R23: 4.7k; R0402; MPN 0402WGF4701TCE; LCSC C25900
R26: 10k; R0402; MPN 0402WGF1002TCE; LCSC C25744
SW1: BOOT/BIND; SW_TS1088; MPN TS-1088R-02026; LCSC C455280
SW2: TX/RX ROLE; SW_SSSS810701; MPN SSSS810701; LCSC C97433
TP1: ESP_EN; TP_1MM; MPN bare pad
TP2: ESP_IO0; TP_1MM; MPN bare pad
TP3: JTAG_TDI; TP_1MM; MPN bare pad
TP4: JTAG_TDO; TP_1MM; MPN bare pad
TP5: PA_TXEN; TP_1MM; MPN bare pad
TP6: PA_RXEN; TP_1MM; MPN bare pad
TP7: RADIO_BUSY; TP_1MM; MPN bare pad
TP8: RADIO_DIO1; TP_1MM; MPN bare pad
TP9: JTAG_TCK; TP_1MM; MPN bare pad
TP10: JTAG_TMS; TP_1MM; MPN bare pad

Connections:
3V3: C20.2, J3.1, J5.1, LED1.4 (VDD), R22.2, R23.2, R26.2; also elsewhere on the board
ESP_EN: TP1.1; also elsewhere on the board
ESP_IO0: SW1.2, TP2.1; also elsewhere on the board
GND: C20.1, J3.2, J5.2, LED1.2 (GND), SW1.1, SW2.1 (TX); also elsewhere on the board
GPIO35: J5.3; also elsewhere on the board
GPIO36: J5.4; also elsewhere on the board
GPIO37: J5.5; also elsewhere on the board
GPIO38: J5.6; also elsewhere on the board
I2C_SCL: J3.6, R23.1; also elsewhere on the board
I2C_SDA: J3.5, R22.1; also elsewhere on the board
JTAG_TCK: TP9.1; also elsewhere on the board
JTAG_TDI: TP3.1; also elsewhere on the board
JTAG_TDO: TP4.1; also elsewhere on the board
JTAG_TMS: TP10.1; also elsewhere on the board
LED_DATA: R15.1; also elsewhere on the board
LED_DIN: LED1.3 (DI), R15.2
PA_RXEN: TP6.1; also elsewhere on the board
PA_TXEN: TP5.1; also elsewhere on the board
RADIO_BUSY: TP7.1; also elsewhere on the board
RADIO_DIO1: TP8.1; also elsewhere on the board
ROLE_SEL: R26.1, SW2.2 (COM); also elsewhere on the board
U0RXD: J3.4; also elsewhere on the board
U0TXD: J3.3; also elsewhere on the board
VBUS: J3.7; also elsewhere on the board

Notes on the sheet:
BOOT / STATUS / ROLE AT RESET
BOTTOM-SIDE GPIO / UART / JTAG / TEST PADS
SW2 low=TX, high=RX. Sample only at reset; firmware changes role after reboot. RX is the open-switch default.
J5 GPIO35/36/37/38 are 3.3V bidirectional GPIO on this S3 N8 module. Headers are not 5V tolerant.
BOOT/BIND on GPIO0. Reset via TP1. USB flashing is normal; UART0 pads provide recovery.
J3: 3.3V logic. 5V is USB output after F1; do not backfeed USB.
